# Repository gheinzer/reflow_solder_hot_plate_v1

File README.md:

# Reflow Soldering Hot Plate (v1)
⚠️ This is not finished yet, I've just ordered the parts and I'm now waiting for them to arrive.

## About this project
I have a pretty bad soldering iron at home (it was very cheap and I once bought it in a local store). After trying (and failing) to solder small SMD components to a PCB, I wanted
to find some other solution to this problem.

So I looked at https://github.com/AfterEarthLTD/Solder-Reflow-Plate/ and https://github.com/DerSpatz/PCB-reflow-solder-heat-plate. These projects seem great to me, but they have one downside:
The actual usable, heated area seems to be quite small. And with that, the idea for this project was born.

## Note
I'm an electrical engineering apprentice, so I'm happy to learn about the mistakes I made when designing this :).

## Features
- ❇️ Separate hot plate and driver PCBs
- 🤏 Maximum PCB size: 100.0x100.0 mm (so it's cheap to order from JLCPCB)
- ♨️ Useable heated area for a rectangular PCB: ca. 84.0x73.0 mm
  - I know this is not that great, but the heater PCB can be swapped out independently of the driver. 
- 🔌 24V power supply input
- 📏 4-wire-voltage measurement for the heating element (used to calculate the temperature)
- ⚡ Current measurement and -regulation for variable-speed temperature transitions
- 📟 Built-in LCD display with adjustable contrast
- ↕️ 3 Buttons for navigation
- ⏱️ Theoretically fast heat-up-times (~4A max. heating current)

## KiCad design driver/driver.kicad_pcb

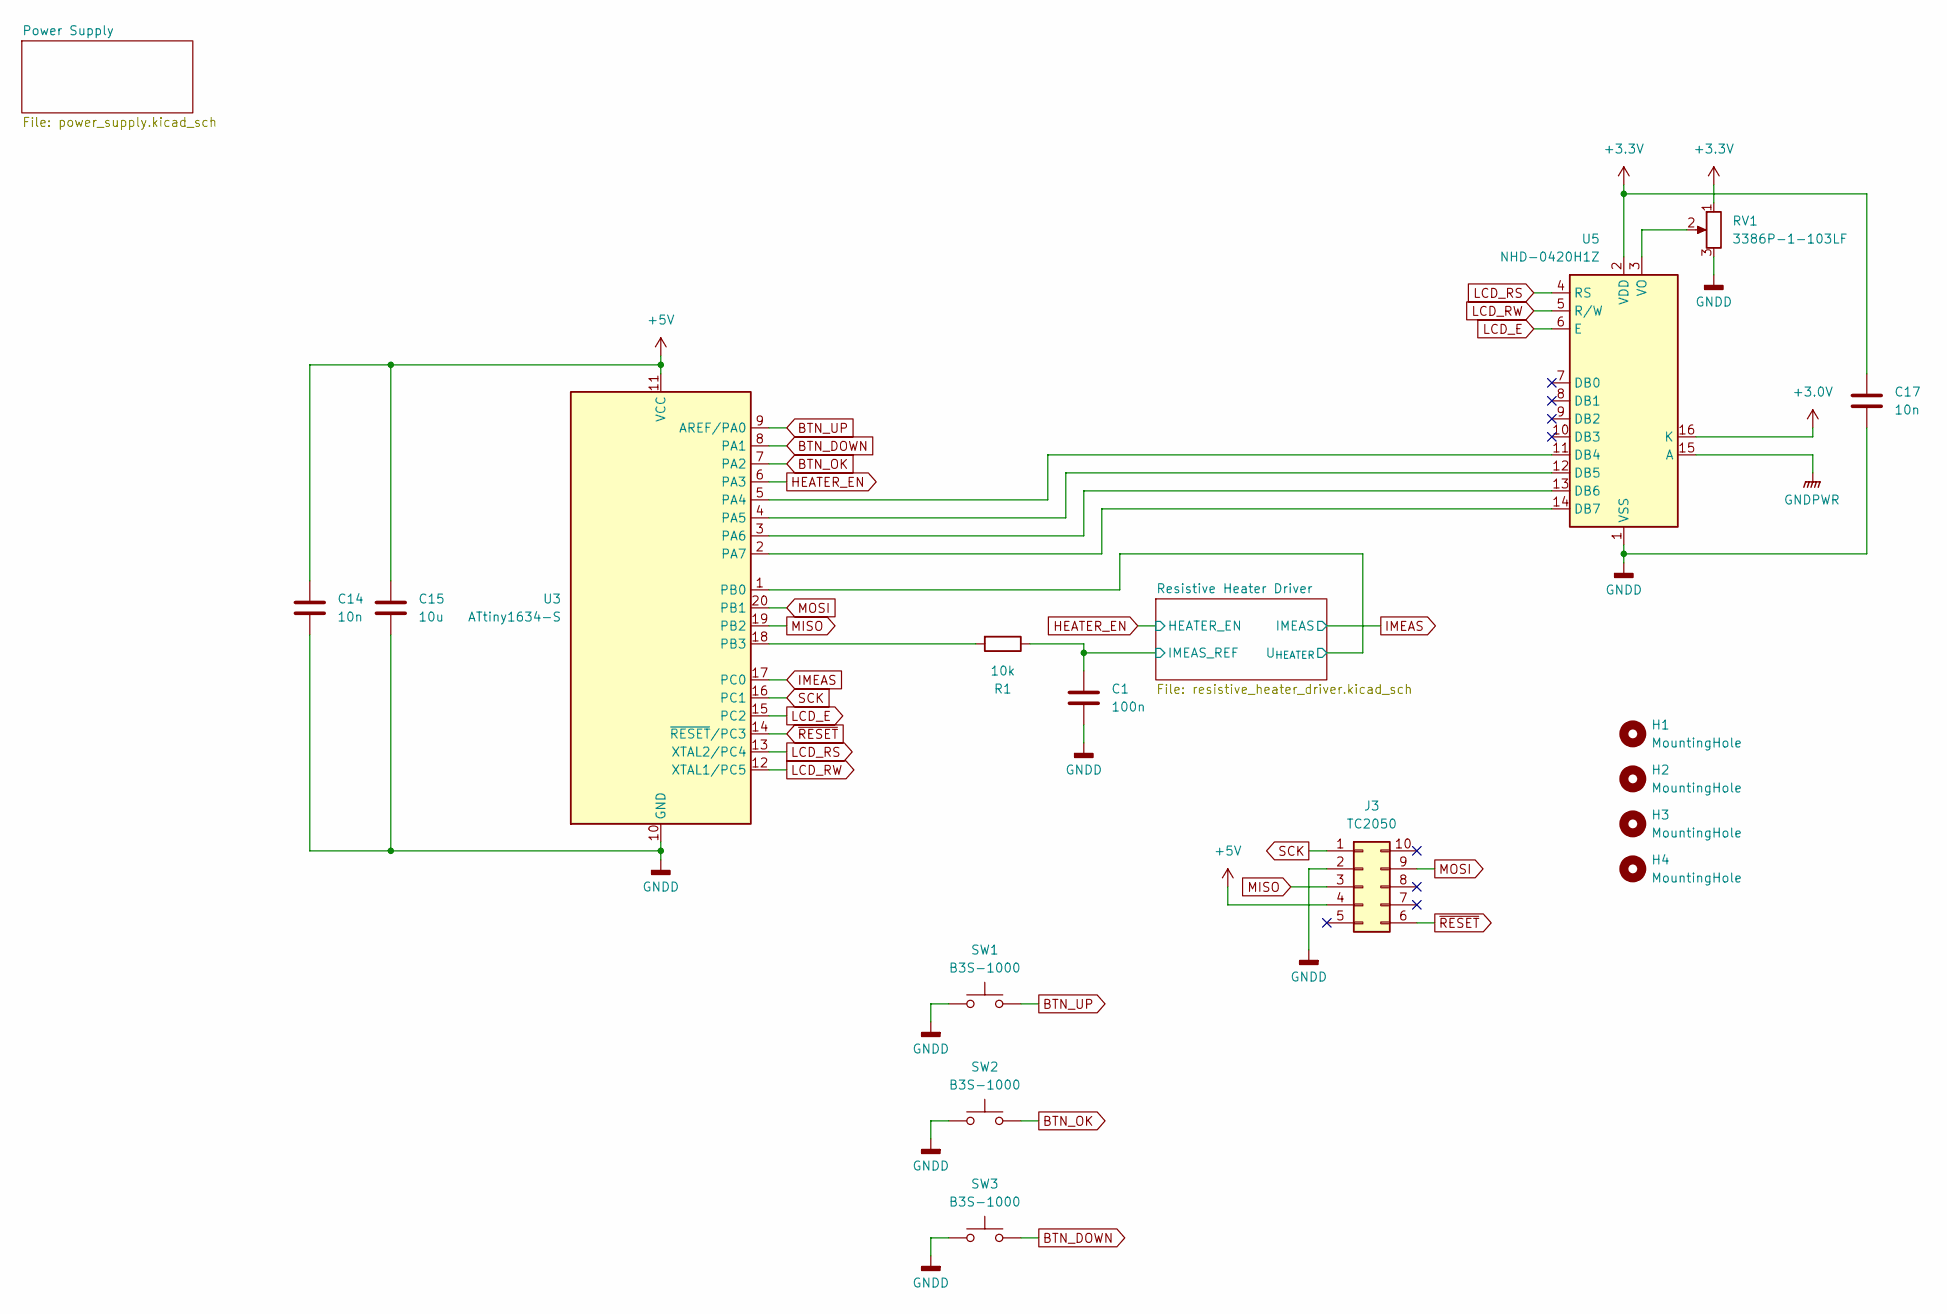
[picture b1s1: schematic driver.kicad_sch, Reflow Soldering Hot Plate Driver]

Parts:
C1: 100n; C_0805_2012Metric_Pad1.18x1.45mm_HandSolder
C14, C17: 10n; C_0805_2012Metric_Pad1.18x1.45mm_HandSolder
C15: 10u; C_0805_2012Metric_Pad1.18x1.45mm_HandSolder
H1, H2, H3, H4: MountingHole; MountingHole_3.2mm_M3
J3: TC2050; Tag-Connect_TC2050-IDC-FP_2x05_P1.27mm_Vertical
R1: 10k; R_0805_2012Metric_Pad1.20x1.40mm_HandSolder
RV1: 3386P-1-103LF; Potentiometer_Bourns_3386P_Vertical
SW1, SW2, SW3: B3S-1000; SW_SPST_B3S-1000
U3: ATtiny1634-S; SOIC-20W_7.5x12.8mm_P1.27mm
U5: NHD-0420H1Z

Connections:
+3.0V: U5.16 (K); also elsewhere on the board
+3.3V: C17.1, RV1.1, U5.2 (VDD); also elsewhere on the board
+5V: C14.1, C15.1, J3.4, U3.11 (VCC); also elsewhere on the board
/Resistive Heater Driver/IMEAS_REF: C1.1, R1.1; also elsewhere on the board
/Resistive Heater Driver/U_{HEATER}: U3.1 (PB0); also elsewhere on the board
BTN_DOWN: SW3.1, U3.8 (PA1)
BTN_OK: SW2.1, U3.7 (PA2)
BTN_UP: SW1.1, U3.9 (AREF/PA0)
GNDD: C1.2, C14.2, C15.2, C17.2, J3.2, RV1.3, SW1.2, SW2.2, SW3.2, U3.10 (GND), U5.1 (VSS); also elsewhere on the board
GNDPWR: U5.15 (A); also elsewhere on the board
HEATER_EN: U3.6 (PA3); also elsewhere on the board
IMEAS: U3.17 (PC0); also elsewhere on the board
LCD_E: U3.15 (PC2), U5.6 (E)
LCD_RS: U3.13 (XTAL2/PC4), U5.4 (RS)
LCD_RW: U3.12 (XTAL1/PC5), U5.5 (R/W)
MISO: J3.3, U3.19 (PB2)
MOSI: J3.9, U3.20 (PB1)
unnamed: U3.5 (PA4), U5.11 (DB4)
unnamed: U3.4 (PA5), U5.12 (DB5)
unnamed: U3.3 (PA6), U5.13 (DB6)
unnamed: U3.2 (PA7), U5.14 (DB7)
unnamed: R1.2, U3.18 (PB3)
unnamed: RV1.2, U5.3 (VO)
SCK: J3.1, U3.16 (PC1)
~RESET: J3.6, U3.14 (~RESET/PC3)

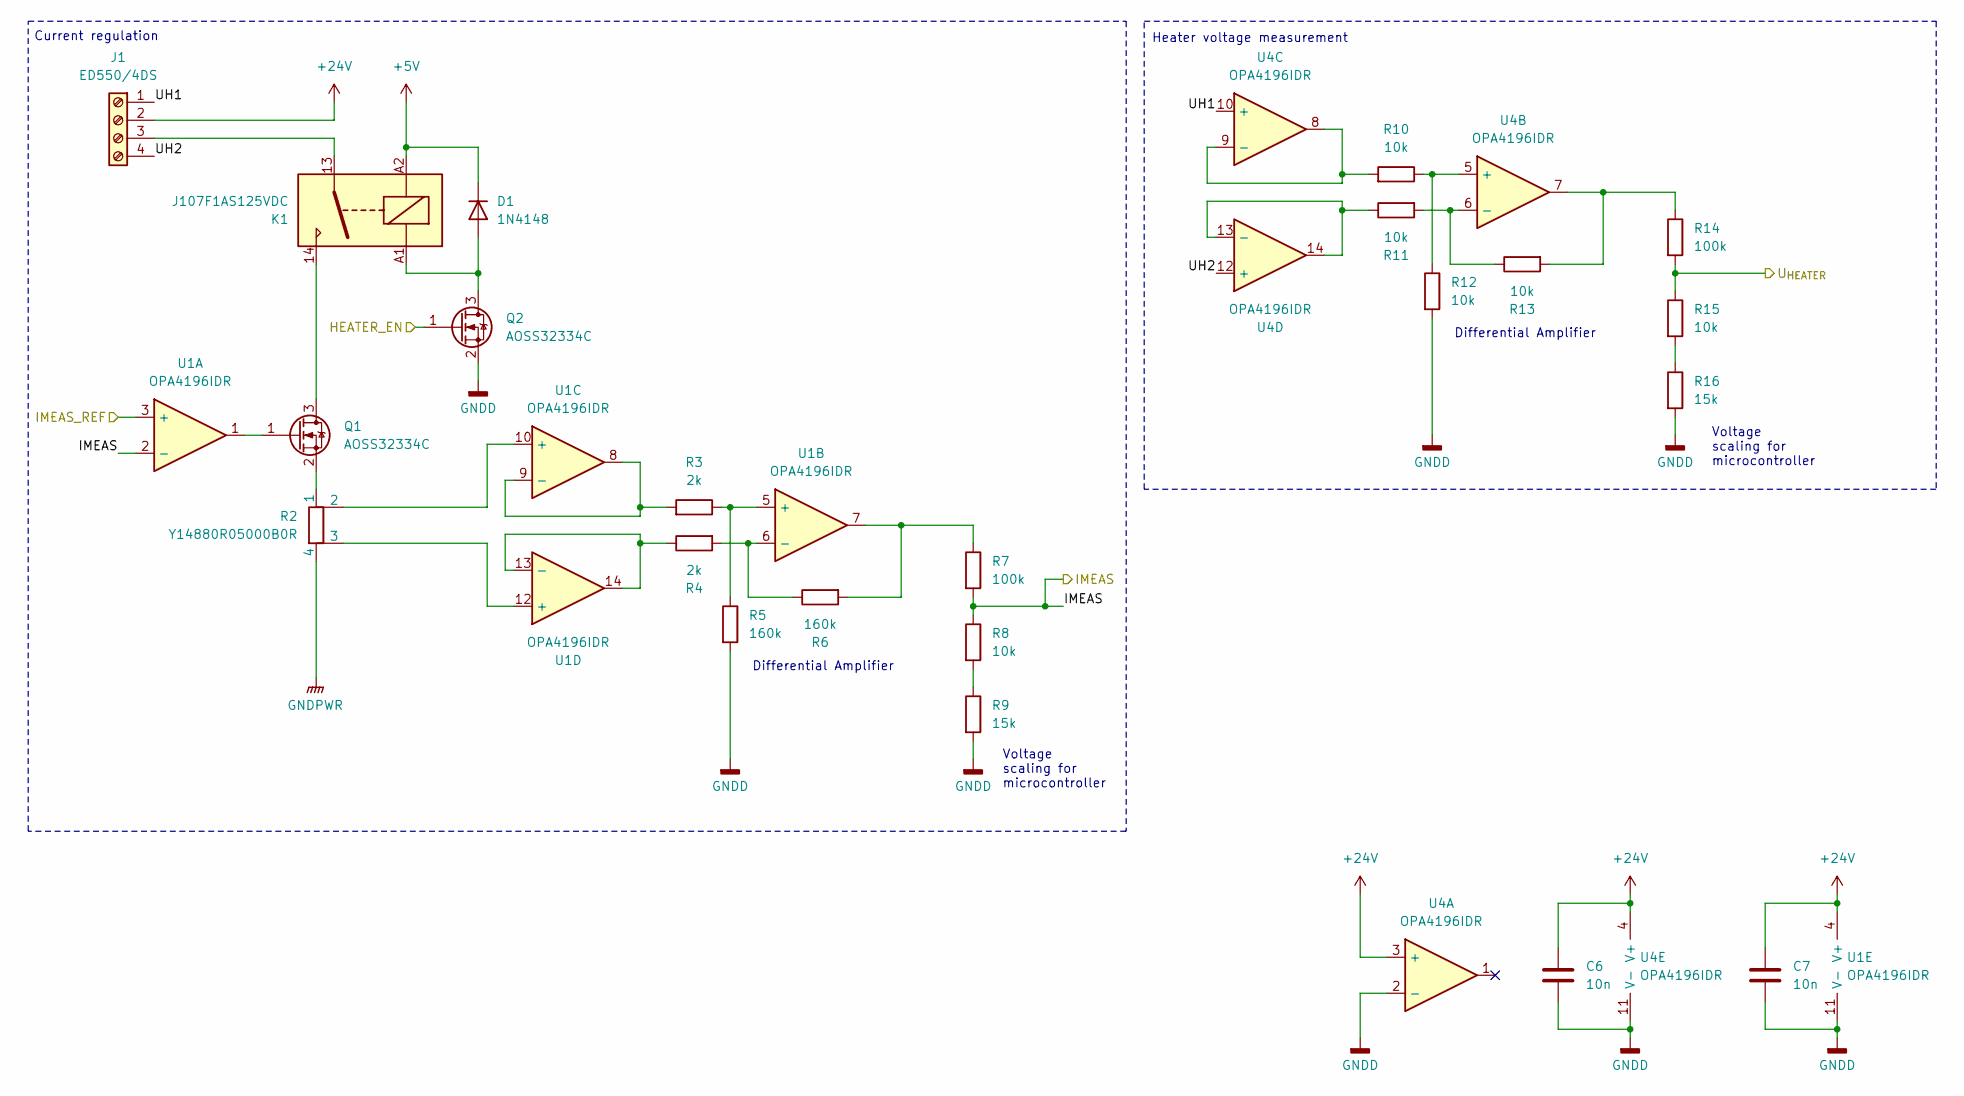
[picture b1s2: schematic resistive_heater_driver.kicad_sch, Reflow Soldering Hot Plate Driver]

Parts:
C6, C7: 10n; C_0805_2012Metric_Pad1.18x1.45mm_HandSolder
D1: 1N4148; D_DO-35_SOD27_P7.62mm_Horizontal
J1: ED550/4DS; TerminalBlock_OnShore_ED550_4DS
K1: J107F1AS125VDC; Relay_CIT_J107F1A
Q1, Q2: AOSS32334C; SOT-23-3
R2: Y14880R05000B0R; R_Shunt_VFR_Y14880Rxxxxxxxx
R3, R4: 2k; R_0805_2012Metric_Pad1.20x1.40mm_HandSolder
R5, R6: 160k; R_0805_2012Metric_Pad1.20x1.40mm_HandSolder
R7, R14: 100k; R_0805_2012Metric_Pad1.20x1.40mm_HandSolder
R8, R10, R11, R12, R13, R15: 10k; R_0805_2012Metric_Pad1.20x1.40mm_HandSolder
R9, R16: 15k; R_0805_2012Metric_Pad1.20x1.40mm_HandSolder
U1, U4: OPA4196IDR; SOIC-14_3.9x8.7mm_P1.27mm

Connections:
+5V: D1.1 (K), K1.A2; also elsewhere on the board
+24V: C6.1, C7.1, J1.2, U1.4 (V+), U4.3 (+), U4.4 (V+); also elsewhere on the board
/Resistive Heater Driver/IMEAS_REF: U1.3 (+); also elsewhere on the board
/Resistive Heater Driver/UH1: J1.1, U4.10 (+)
/Resistive Heater Driver/UH2: J1.4, U4.12 (+)
/Resistive Heater Driver/U_{HEATER}: R14.2, R15.1; also elsewhere on the board
GNDD: C6.2, C7.2, Q2.2 (S), R5.2, R9.2, R12.2, R16.2, U1.11 (V-), U4.2 (-), U4.11 (V-); also elsewhere on the board
GNDPWR: R2.4; also elsewhere on the board
HEATER_EN: Q2.1 (G); also elsewhere on the board
IMEAS: R7.2, R8.1, U1.2 (-); also elsewhere on the board
unnamed: D1.2 (A), K1.A1, Q2.3 (D)
unnamed: J1.3, K1.13
unnamed: K1.14, Q1.3 (D)
unnamed: Q1.1 (G), U1.1
unnamed: Q1.2 (S), R2.1
unnamed: R6.2, R7.1, U1.7
unnamed: R8.2, R9.1
unnamed: R13.2, R14.1, U4.7
unnamed: R15.2, R16.1
unnamed: R3.1, R5.1, U1.5 (+)
unnamed: R4.2, R6.1, U1.6 (-)
unnamed: R2.2, U1.10 (+)
unnamed: R3.2, U1.8, U1.9 (-)
unnamed: R2.3, U1.12 (+)
unnamed: R4.1, U1.13 (-), U1.14
unnamed: R10.1, R12.1, U4.5 (+)
unnamed: R11.2, R13.1, U4.6 (-)
unnamed: R10.2, U4.8, U4.9 (-)
unnamed: R11.1, U4.13 (-), U4.14

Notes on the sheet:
Differential Amplifier
Current regulation
Heater voltage measurement
Voltage scaling for microcontroller

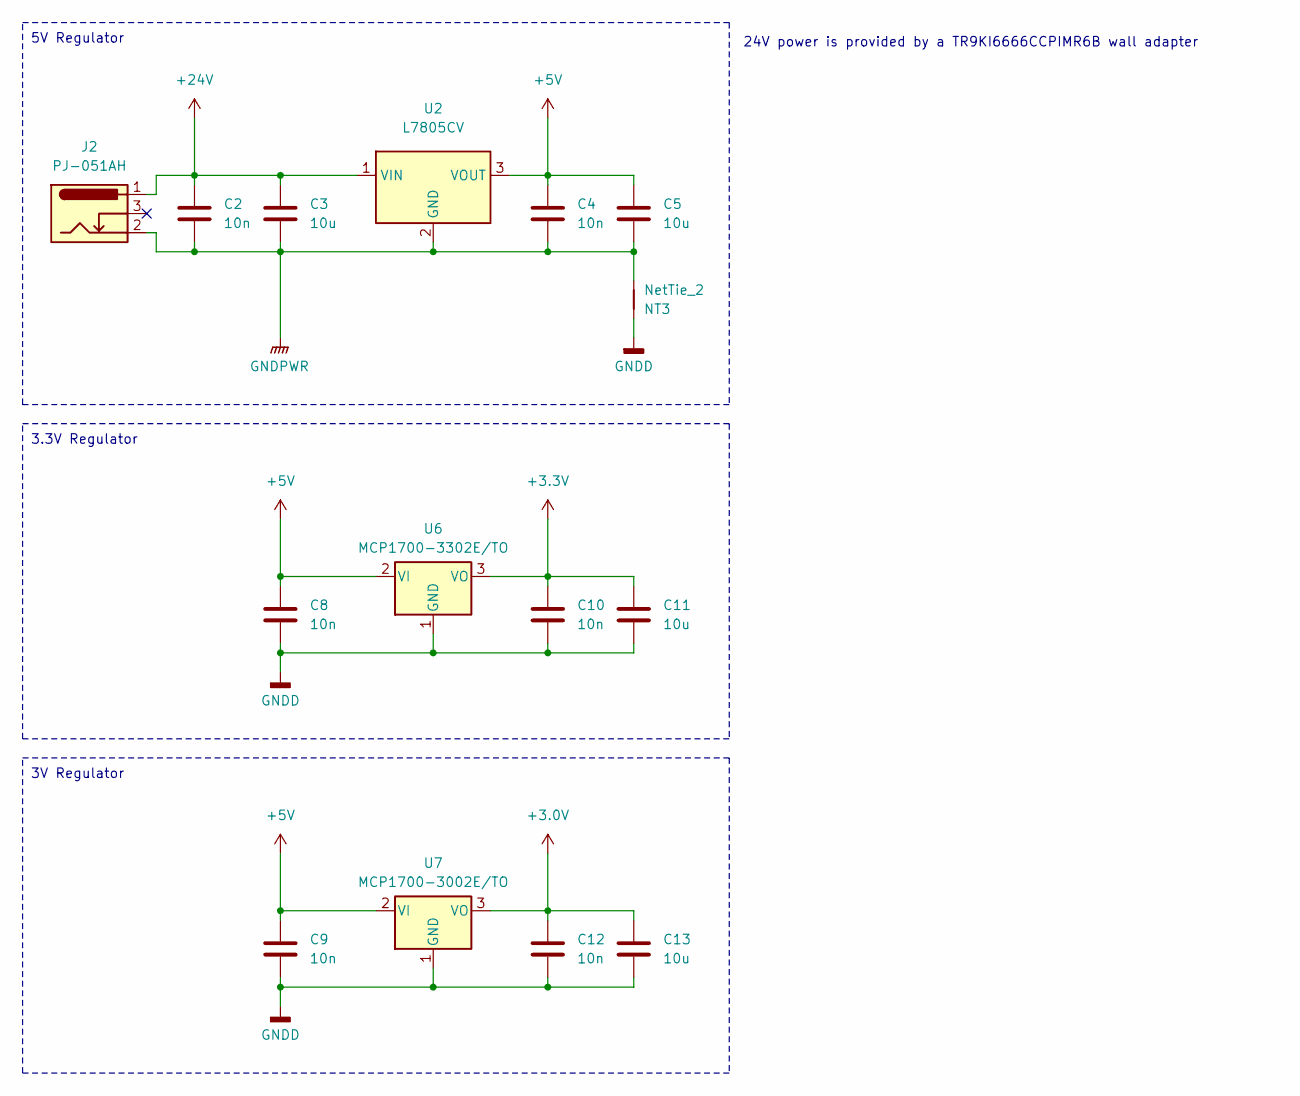
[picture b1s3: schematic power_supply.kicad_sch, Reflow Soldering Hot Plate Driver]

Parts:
C2, C4, C8, C9, C10, C12: 10n; C_0805_2012Metric_Pad1.18x1.45mm_HandSolder
C3, C5, C11, C13: 10u; C_0805_2012Metric_Pad1.18x1.45mm_HandSolder
J2: PJ-051AH; BarrelJack_CUI_PJ-079BH_Horizontal
NT3: NetTie_2; NetTie-2_THT_Pad1.0mm
U2: L7805CV; TO-220-3_Horizontal_TabDown
U6: MCP1700-3302E/TO; TO-92_Inline
U7: MCP1700-3002E/TO; TO-92_Inline

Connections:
+3.0V: C12.1, C13.1, U7.3 (VO); also elsewhere on the board
+3.3V: C10.1, C11.1, U6.3 (VO); also elsewhere on the board
+5V: C4.1, C5.1, C8.1, C9.1, U2.3 (VOUT), U6.2 (VI), U7.2 (VI); also elsewhere on the board
+24V: C2.1, C3.1, J2.1, U2.1 (VIN); also elsewhere on the board
GNDD: C8.2, C9.2, C10.2, C11.2, C12.2, C13.2, NT3.2, U6.1 (GND), U7.1 (GND); also elsewhere on the board
GNDPWR: C2.2, C3.2, C4.2, C5.2, J2.2, NT3.1, U2.2 (GND); also elsewhere on the board

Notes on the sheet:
5V Regulator
3V Regulator
24V power is provided by a TR9KI6666CCPIMR6B wall adapter
3.3V Regulator

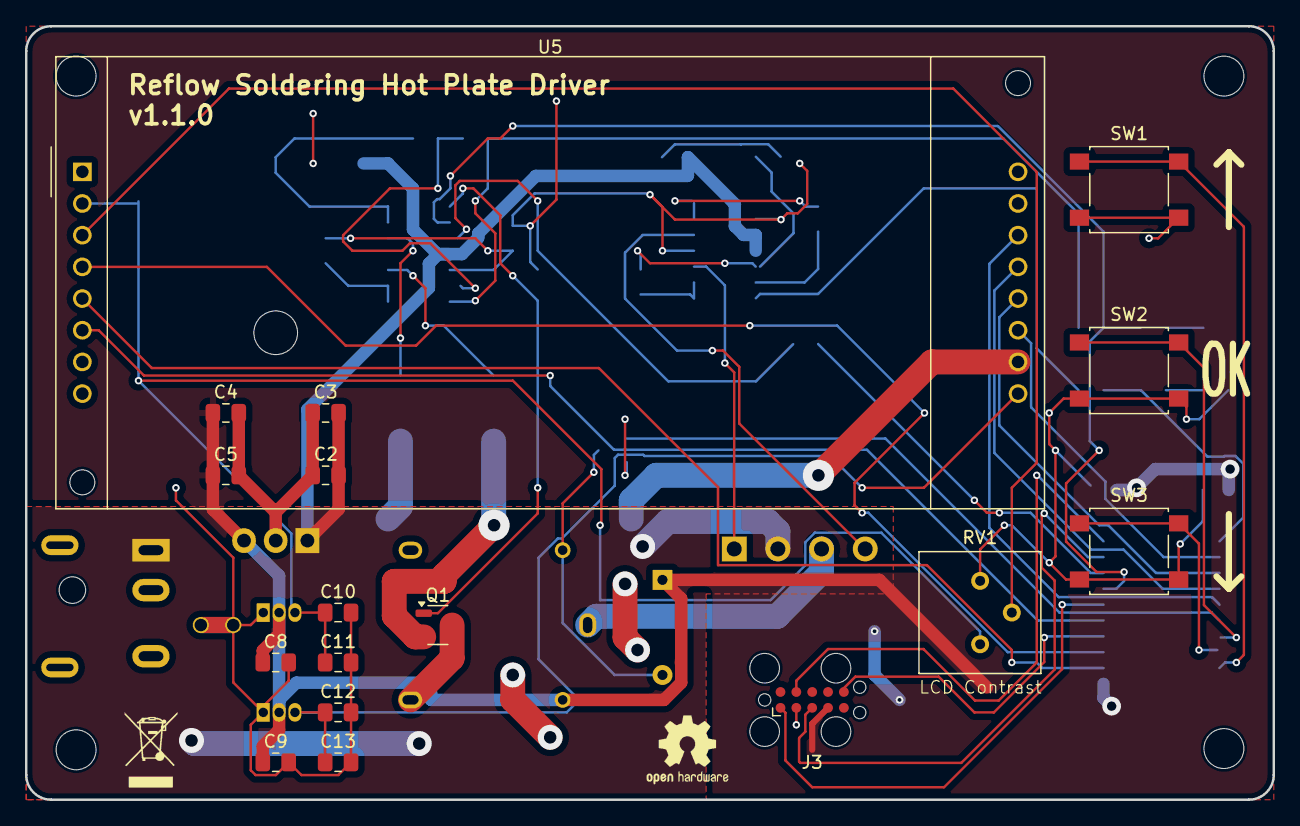
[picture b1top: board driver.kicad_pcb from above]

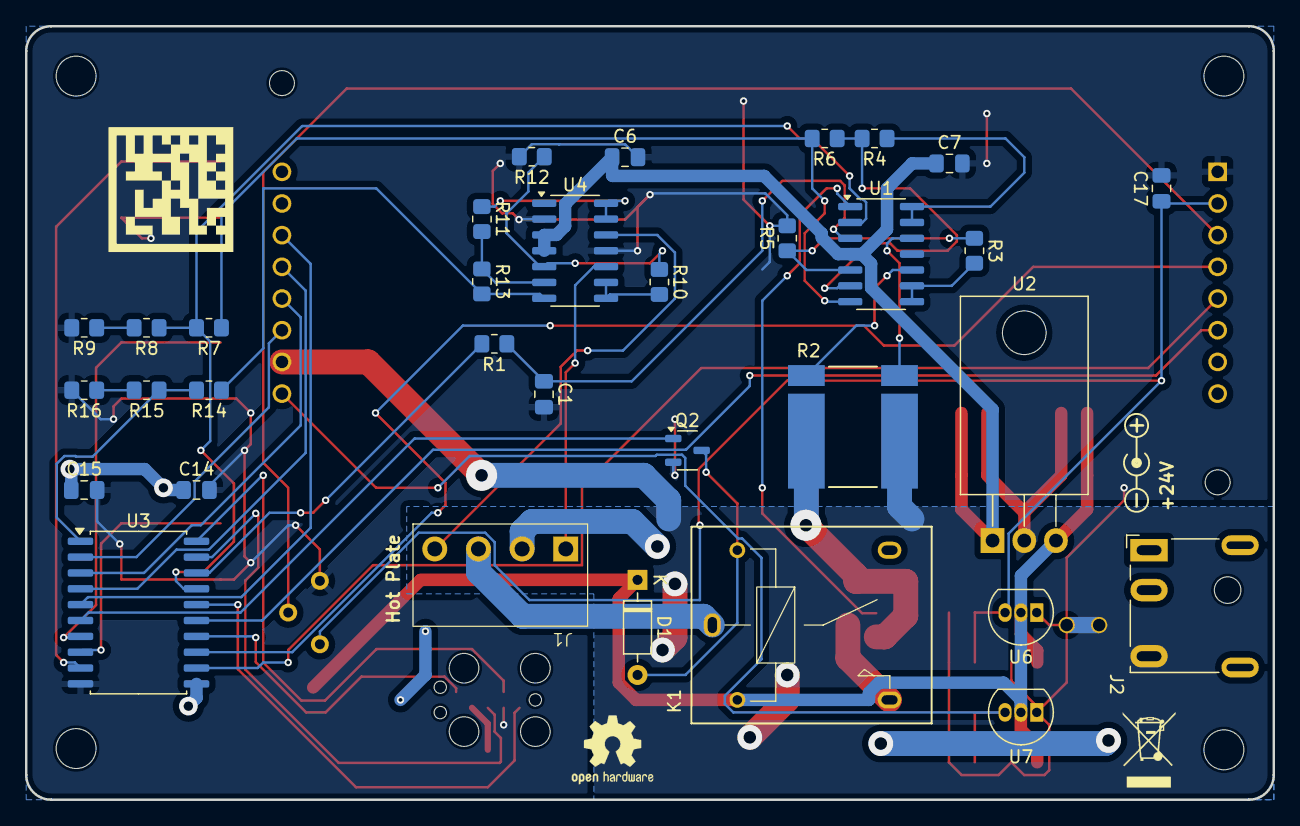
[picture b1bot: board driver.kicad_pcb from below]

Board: 2 copper layers, 100.0 x 62.0 mm, 55 parts (33 on the bottom side), 47 nets.

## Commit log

2024-08-01 Added existing project to git repository
2024-08-01 Added the CERN OHL as a LICENSE
2024-08-01 Added data matrix codes to PCBs for easy identification
2024-08-02 Replaced 5V regulator with fully compatible alternative
